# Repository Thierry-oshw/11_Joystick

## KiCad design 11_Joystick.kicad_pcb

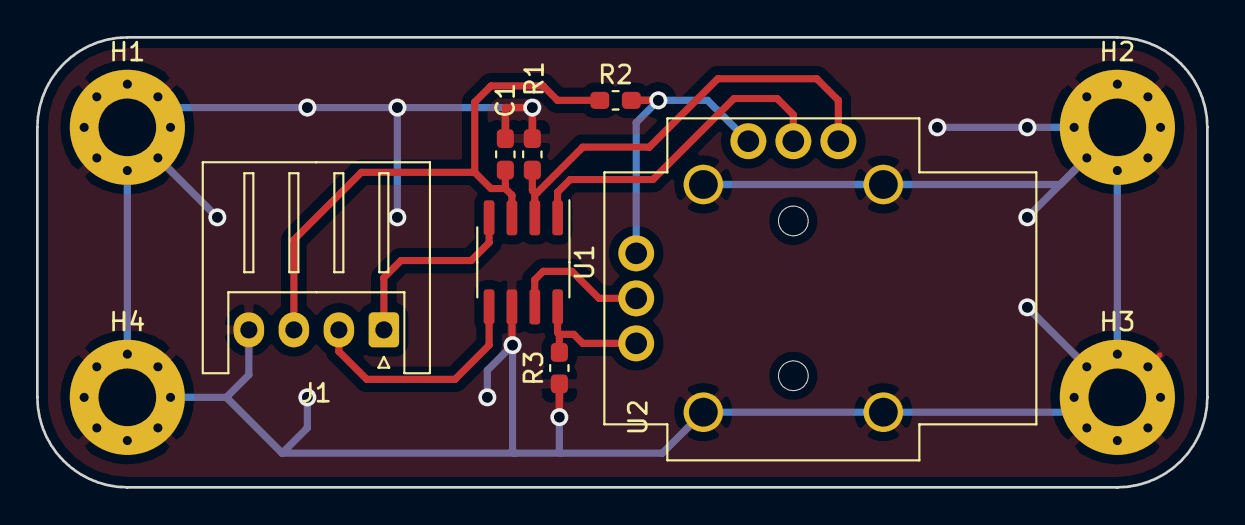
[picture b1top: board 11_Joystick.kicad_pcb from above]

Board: 2 copper layers, 65.0 x 25.0 mm, 11 parts (0 on the bottom side), 9 nets.

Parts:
C1: 100nF; C_0603_1608Metric_Pad1.05x0.95mm_HandSolder
H1, H2, H3, H4: MountingHole_Pad; MountingHole_3.2mm_M3_Pad_Via
J1: Conn_01x04; JST_XH_S4B-XH-A_1x04_P2.50mm_Horizontal
R1, R2, R3: 10k; R_0603_1608Metric_Pad1.05x0.95mm_HandSolder
U1: MCP3426-xSN; SOIC-8_3.9x4.9mm_P1.27mm
U2: joystick; RKJXV1220

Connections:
3V3: C1.1, J1.3, R2.1, U1.3
GND: C1.2, H1.1, H2.1, H3.1, H4.1, J1.4, R1.1, R3.1, U1.6, U2.7, U2.8, U2.9, U2.10
unnamed: R2.2, U2.3, U2.4
SCL: J1.2, U1.5
SDA: J1.1, U1.4
mes0_0: R3.2, U1.8, U2.6
mes0_1: U1.7, U2.5
mes1_0: R1.2, U1.2, U2.1
mes1_1: U1.1, U2.2

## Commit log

2021-04-13 schema, placement, routage
2021-07-24 maj split librairie
2023-05-02 chgt nom fichier licence
